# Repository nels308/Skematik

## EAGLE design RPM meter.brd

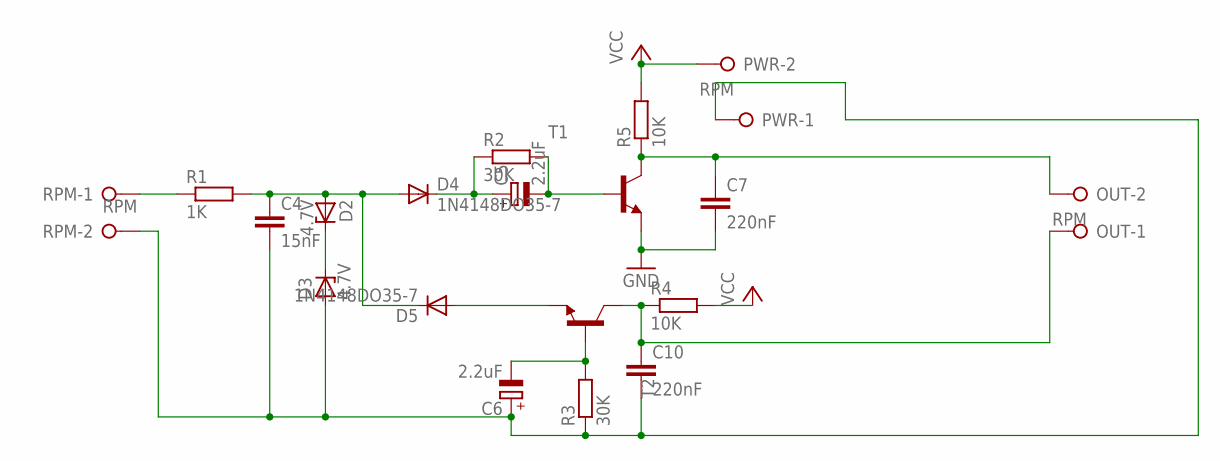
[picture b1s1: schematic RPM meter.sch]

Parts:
C4: 15nF; C025-024X044
C5, C6: 2.2uF; E1,8-4
C7, C10: 220nF; C025-024X044
D2, D3: 4.7V; ZDIO-10
D4, D5: 1N4148DO35-7; DO35-7
OUT: RPM; W237-132
PWR: RPM; W237-132
R1: 1K; 0207/7
R2, R3: 30K; 0207/7
R4, R5: 10K; 0207/7
RPM: RPM; W237-132
T1, T2: 2N2222-NPN-TO92-EBC; TO92-EBC

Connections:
GND: C7.2, T1.E
unnamed: C4.2, C6.+, C10.2, D3.A, PWR.1, R3.1, RPM.2
unnamed: R1.1, RPM.1
unnamed: C4.1, D2.A, D4.A, D5.C, R1.2
unnamed: C7.1, OUT.2, R5.1, T1.C
unnamed: D2.C, D3.C
unnamed: C5.+, D4.C, R2.1
unnamed: C5.-, R2.2, T1.B
unnamed: D5.A, T2.E
unnamed: C6.-, R3.2, T2.B
unnamed: C10.1, OUT.1, R4.1, T2.C
VCC: PWR.2, R4.2, R5.2

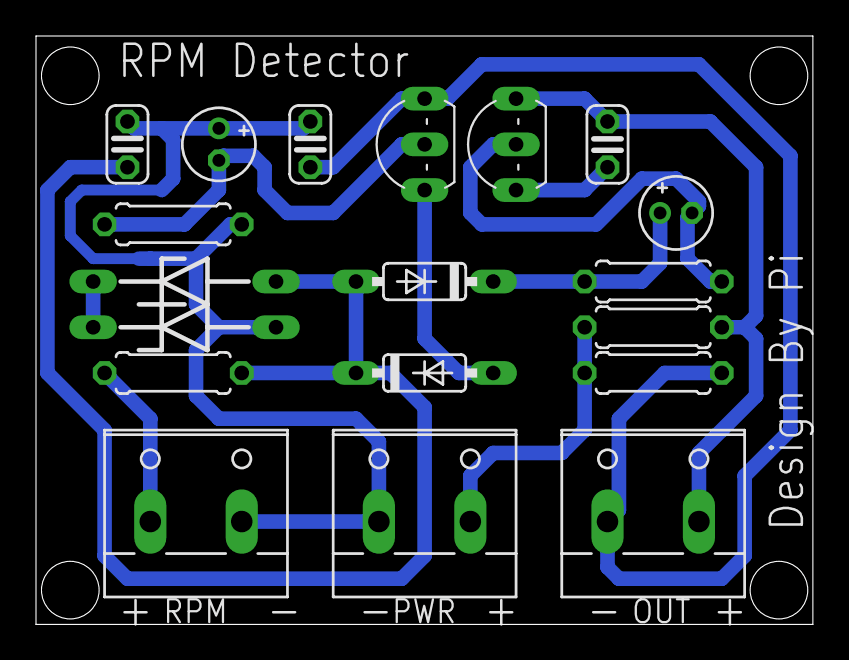
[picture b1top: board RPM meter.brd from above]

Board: 2 copper layers, 43.2 x 32.7 mm, 19 parts (0 on the bottom side), 12 nets.
